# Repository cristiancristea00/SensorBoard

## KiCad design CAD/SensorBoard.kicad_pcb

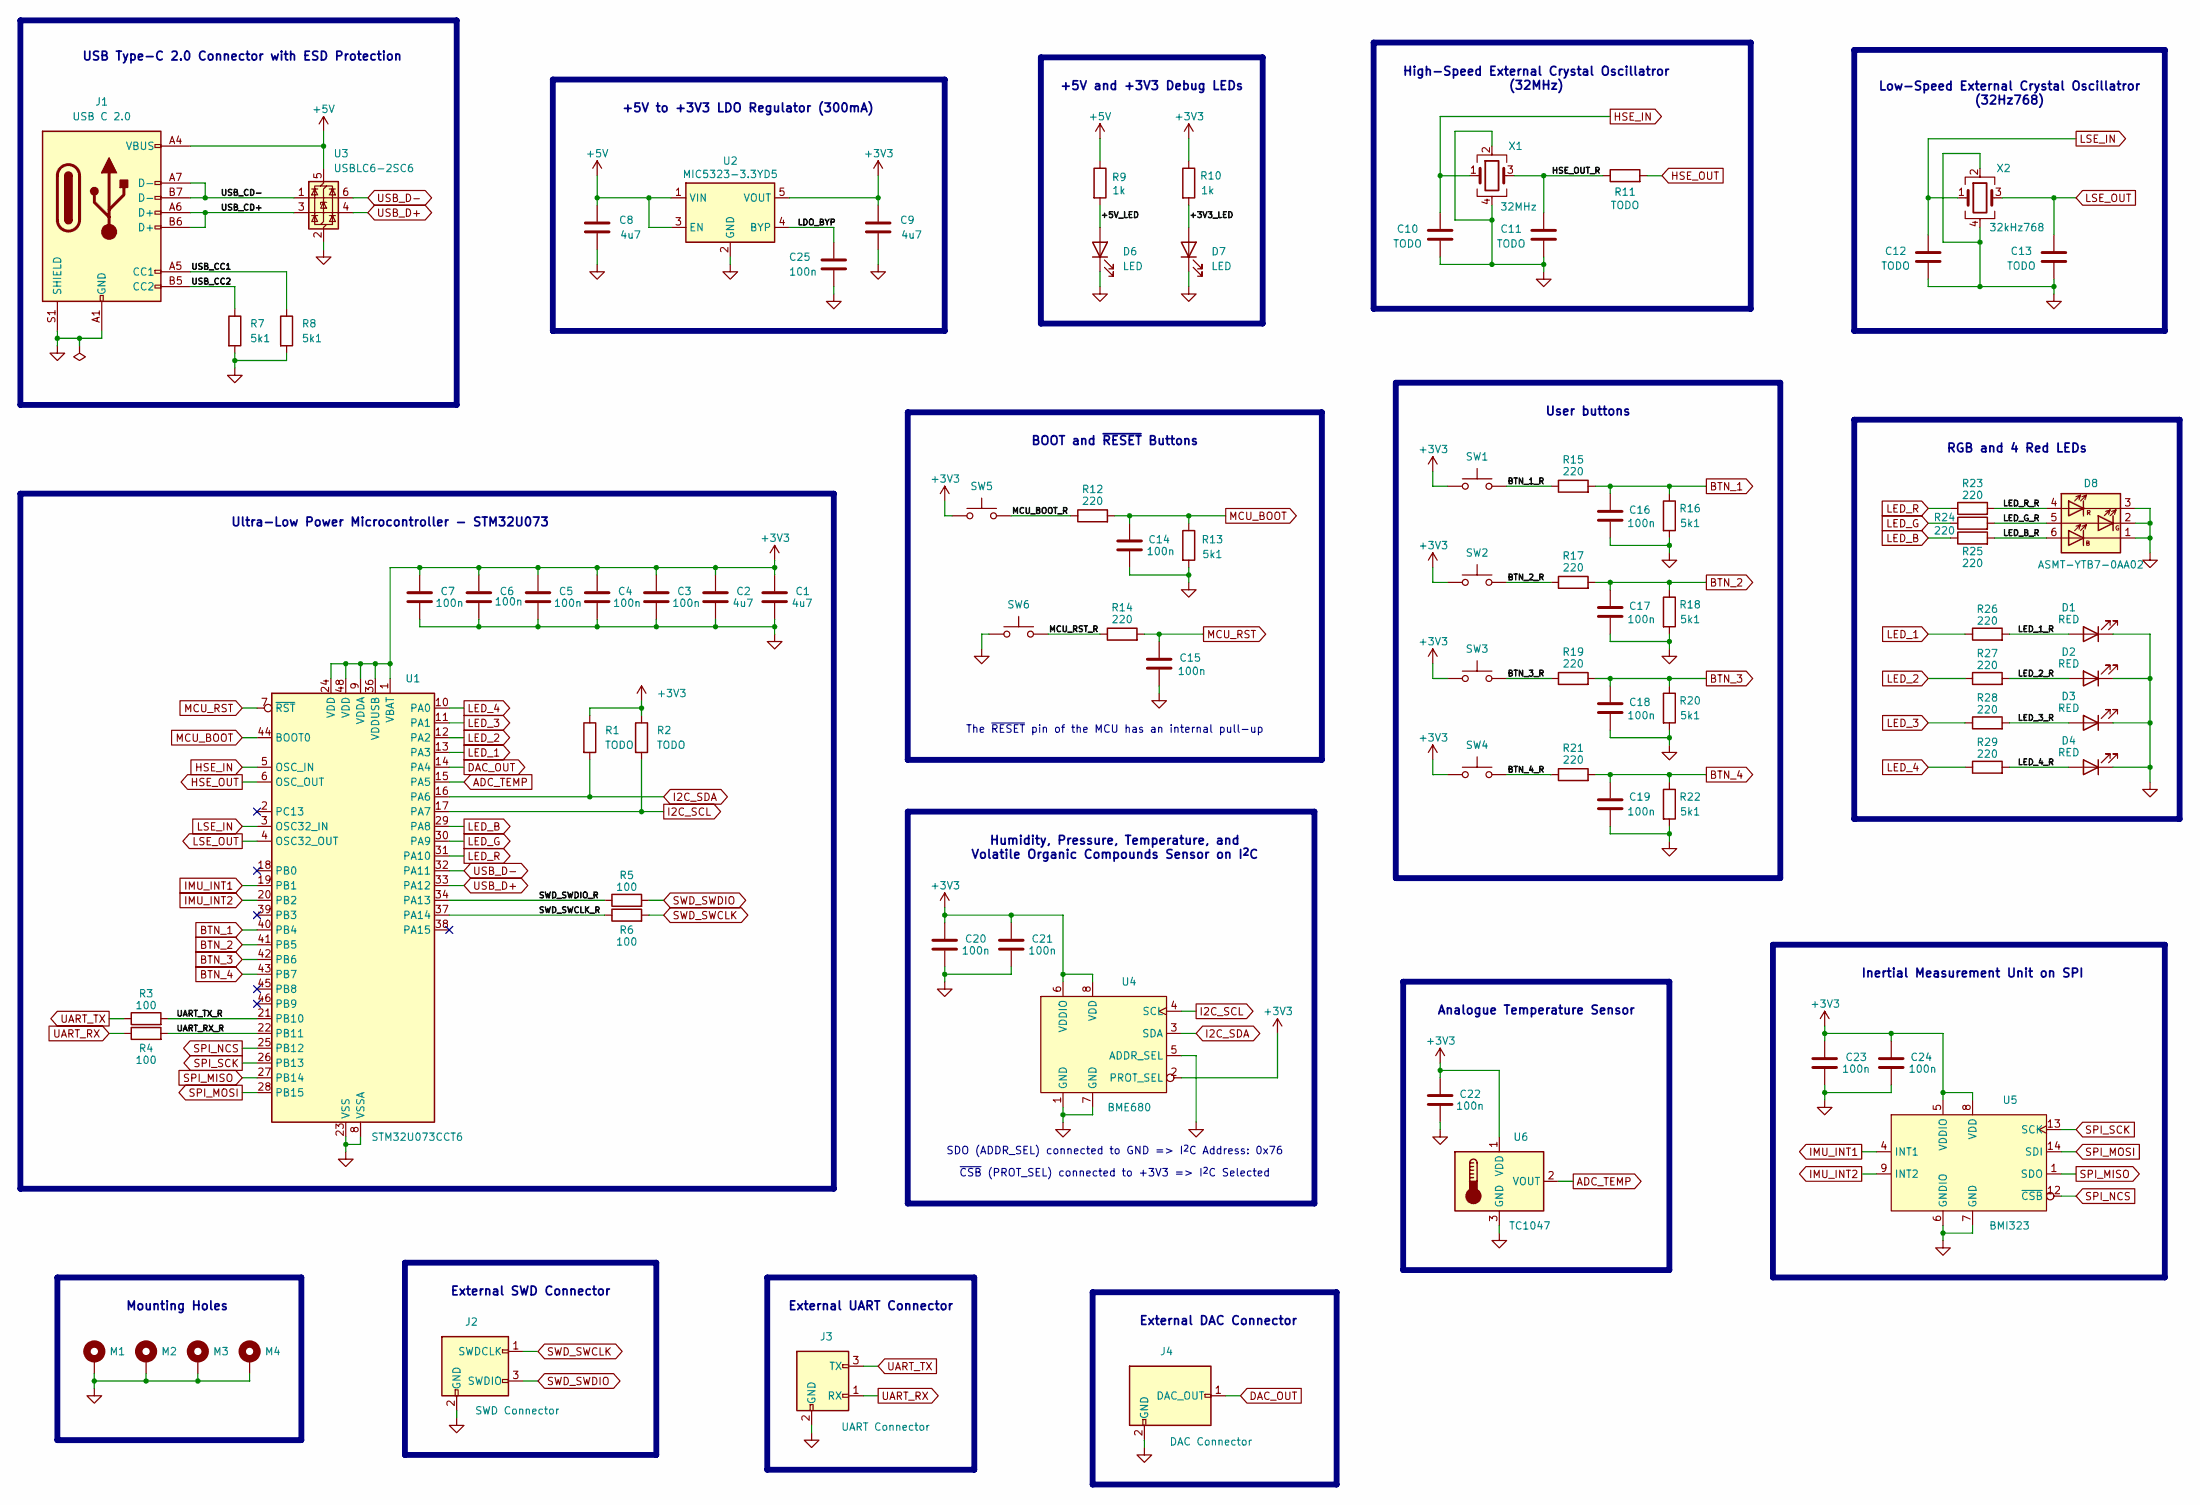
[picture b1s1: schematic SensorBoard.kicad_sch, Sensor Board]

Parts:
C1, C2, C8, C9: 4u7; C_0603_1608Metric
C3, C4, C5, C6, C7, C14, C15, C16, C17, C18, C19, C20, C21, C22, C23, C24: 100n; C_0402_1005Metric
C10, C11, C12, C13: TODO; C_0402_1005Metric
C25: 100n; C_0603_1608Metric
D1, D2, D3, D4: RED; LED_0805_2012Metric
D6, D7: LED; LED_0805_2012Metric
D8: ASMT-YTB7-0AA02
J1: USB C 2.0; USB_C_Receptacle_GCT_USB4105-xx-A_16P_TopMnt_Horizontal
J2: SWD Connector; SM03B-SR
J3: UART Connector; SM03B-SR
J4: DAC Connector; SM02B-SR
M1: M1; MountingHole_3.2mm_M3_Pad_Via
M2: M2; MountingHole_3.2mm_M3_Pad_Via
M3: M3; MountingHole_3.2mm_M3_Pad_Via
M4: M4; MountingHole_3.2mm_M3_Pad_Via
R1, R2, R11: TODO; R_0402_1005Metric
R3, R4, R5, R6: 100; R_0402_1005Metric
R7, R8, R13, R16, R18, R20, R22: 5k1; R_0402_1005Metric
R9, R10: 1k; R_0402_1005Metric
R12, R14, R15, R17, R19, R21, R23, R24, R25, R26, R27, R28, R29: 220; R_0402_1005Metric
SW1: SW_1; PTS636-SM25F-SMTR-LFS
SW2: SW_2; PTS636-SM25F-SMTR-LFS
SW3: SW_3; PTS636-SM25F-SMTR-LFS
SW4: SW_4; PTS636-SM25F-SMTR-LFS
SW5: SW_BOOT; PTS636-SM25F-SMTR-LFS
SW6: SW_RST; PTS636-SM25F-SMTR-LFS
U1: STM32U073CCT6; LQFP-48_7x7mm_P0.5mm
U2: MIC5323-3.3YD5; SOT-23-5
U3: USBLC6-2SC6; SOT-23-6
U4: BME680; BME630
U5: BMI323
U6: TC1047; SOT-23-3
X1: 32MHz; Crystal_SMD_2016-4Pin_2.0x1.6mm
X2: 32kHz768; Crystal_SMD_2016-4Pin_2.0x1.6mm

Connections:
+3V3: C1.2, C2.2, C3.2, C4.2, C5.2, C6.2, C7.2, C9.2, C20.2, C21.2, C22.2, C23.2, C24.2, R1.1, R2.1, R10.1, SW1.1, SW2.1, SW3.1, SW4.1, SW5.1, U1.1 (VBAT), U1.9 (VDDA), U1.24 (VDD), U1.36 (VDDUSB), U1.48 (VDD), U2.5 (VOUT), U4.2 (PROT_SEL), U4.6 (VDDIO), U4.8 (VDD), U5.5 (VDDIO), U5.8 (VDD), U6.1 (VDD)
+5V: C8.2, J1.A4 (VBUS), J1.A9 (VBUS), J1.B4 (VBUS), J1.B9 (VBUS), R9.1, U2.1 (VIN), U2.3 (EN), U3.5 (VBUS)
/+3V3_LED: D7.2 (A), R10.2
/+5V_LED: D6.2 (A), R9.2
/BTN_1_R: R15.1, SW1.2
/BTN_2_R: R17.1, SW2.2
/BTN_3_R: R19.1, SW3.2
/BTN_4_R: R21.1, SW4.2
/HSE_OUT_R: C11.1, R11.1, X1.3
/LDO_BYP: C25.2, U2.4 (BYP)
/LED_1_R: D1.2 (A), R26.2
/LED_2_R: D2.2 (A), R27.2
/LED_3_R: D3.2 (A), R28.2
/LED_4_R: D4.2 (A), R29.2
/LED_B_R: D8.6 (AB), R25.2
/LED_G_R: D8.5 (AG), R24.2
/LED_R_R: D8.4 (AR), R23.2
/MCU_BOOT_R: R12.1, SW5.2
/MCU_RST_R: R14.1, SW6.2
/SWD_SWCLK_R: R6.1, U1.37 (PA14)
/SWD_SWDIO_R: R5.1, U1.34 (PA13)
/UART_RX_R: R4.2, U1.22 (PB11)
/UART_TX_R: R3.2, U1.21 (PB10)
/USB_CC1: J1.A5 (CC1), R8.1
/USB_CC2: J1.B5 (CC2), R7.1
/USB_CD+: J1.A6 (D+), J1.B6 (D+), U3.3 (I/O2)
/USB_CD-: J1.A7 (D-), J1.B7 (D-), U3.1 (I/O1)
ADC_TEMP: U1.15 (PA5), U6.2 (VOUT)
BTN_1: C16.2, R15.2, R16.1, U1.40 (PB4)
BTN_2: C17.2, R17.2, R18.1, U1.41 (PB5)
BTN_3: C18.2, R19.2, R20.1, U1.42 (PB6)
BTN_4: C19.2, R21.2, R22.1, U1.43 (PB7)
DAC_OUT: J4.1 (DAC_OUT), U1.14 (PA4)
GND: C1.1, C2.1, C3.1, C4.1, C5.1, C6.1, C7.1, C8.1, C9.1, C10.2, C11.2, C12.2, C13.2, C14.1, C15.1, C16.1, C17.1, C18.1, C19.1, C20.1, C21.1, C22.1, C23.1, C24.1, C25.1, D1.1 (K), D2.1 (K), D3.1 (K), D4.1 (K), D6.1 (K), D7.1 (K), D8.1 (KB), D8.2 (KG), D8.3 (KR), J1.A1 (GND), J1.A12 (GND), J1.B1 (GND), J1.B12 (GND), J1.S1 (SHIELD), J2.2 (GND), J3.2 (GND), J4.2 (GND), M1.1, M2.1, M3.1, M4.1, R7.2, R8.2, R13.2, R16.2, R18.2, R20.2, R22.2, SW6.1, U1.8 (VSSA), U1.23 (VSS), U1.35 (VSS), U1.47 (VSS), U2.2 (GND), U3.2 (GND), U4.1 (GND), U4.5 (ADDR_SEL), U4.7 (GND), U5.6 (GNDIO), U5.7 (GND), U6.3 (GND), X1.2, X1.4, X2.2, X2.4
HSE_IN: C10.1, U1.5 (OSC_IN), X1.1
HSE_OUT: R11.2, U1.6 (OSC_OUT)
I2C_SCL: R2.2, U1.17 (PA7), U4.4 (SCL)
I2C_SDA: R1.2, U1.16 (PA6), U4.3 (SDA)
IMU_INT1: U1.19 (PB1), U5.4 (INT1)
IMU_INT2: U1.20 (PB2), U5.9 (INT2)
LED_1: R26.1, U1.13 (PA3)
LED_2: R27.1, U1.12 (PA2)
LED_3: R28.1, U1.11 (PA1)
LED_4: R29.1, U1.10 (PA0)
LED_B: R25.1, U1.29 (PA8)
LED_G: R24.1, U1.30 (PA9)
LED_R: R23.1, U1.31 (PA10)
LSE_IN: C12.1, U1.3 (OSC32_IN), X2.1
LSE_OUT: C13.1, U1.4 (OSC32_OUT), X2.3
MCU_BOOT: C14.2, R12.2, R13.1, U1.44 (BOOT0)
MCU_RST: C15.2, R14.2, U1.7 (~RST)
SPI_MISO: U1.27 (PB14), U5.1 (SDO)
SPI_MOSI: U1.28 (PB15), U5.14 (SDI)
SPI_NCS: U1.25 (PB12), U5.12 (~CSB)
SPI_SCK: U1.26 (PB13), U5.13 (SCK)
SWD_SWCLK: J2.1 (SWDCLK), R6.2
SWD_SWDIO: J2.3 (SWDIO), R5.2
UART_RX: J3.1 (RX), R4.1
UART_TX: J3.3 (TX), R3.1
USB_D+: U1.33 (PA12), U3.4 (I/O2)
USB_D-: U1.32 (PA11), U3.6 (I/O1)

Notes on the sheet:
The ~{RESET} pin of the MCU has an internal pull-up
User buttons
~{CSB} (PROT_SEL) connected to +3V3 => I^{2}C Selected
RGB and 4 Red LEDs
External UART Connector
External DAC Connector
Mounting Holes
+5V to +3V3 LDO Regulator (300mA)
BOOT and ~{RESET} Buttons
External SWD Connector
High-Speed External Crystal Oscillatror (32MHz)
Analogue Temperature Sensor
SDO (ADDR_SEL) connected to GND => I^{2}C Address: 0x76
USB Type-C 2.0 Connector with ESD Protection
Ultra-Low Power Microcontroller - STM32U073
Humidity, Pressure, Temperature, and Volatile Organic Compounds Sensor on I^{2}C
Low-Speed External Crystal Oscillatror (32Hz768)
+5V and +3V3 Debug LEDs
Inertial Measurement Unit on SPI

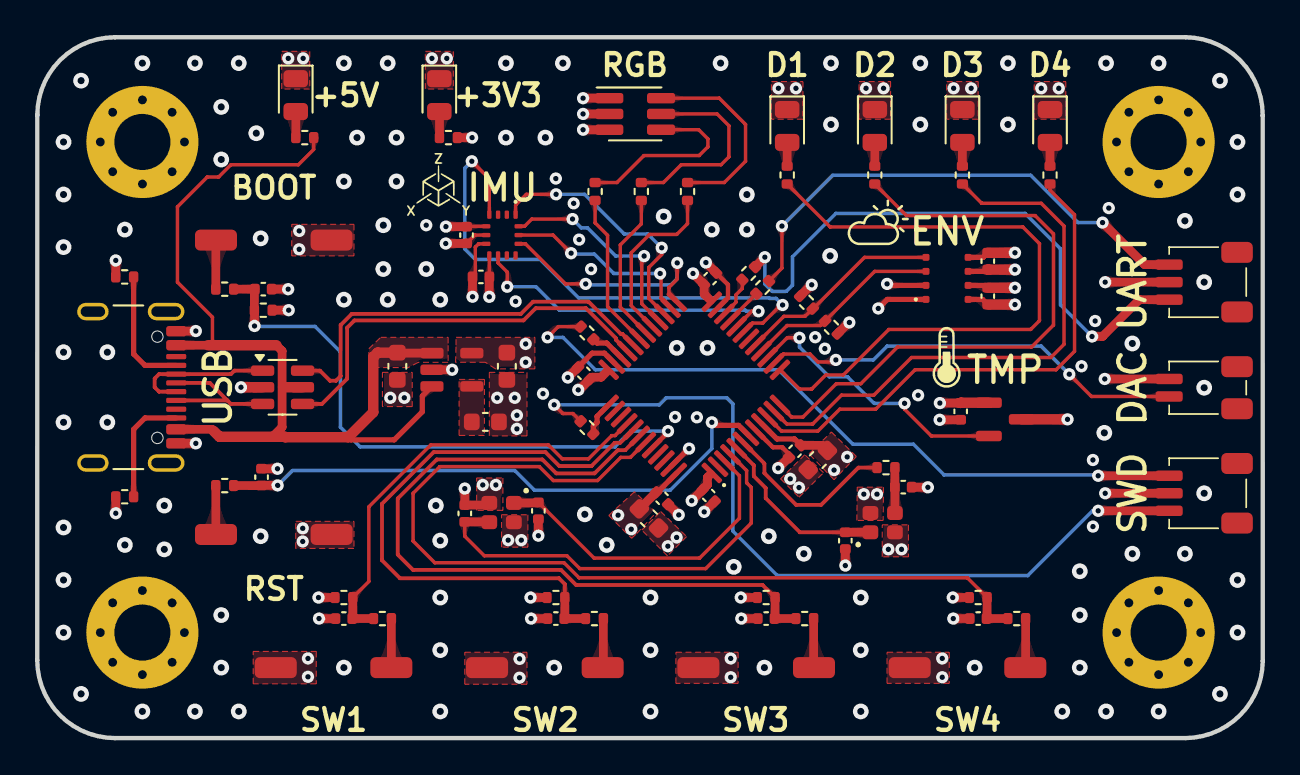
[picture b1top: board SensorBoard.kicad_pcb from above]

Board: 4 copper layers, 69.9 x 40.0 mm, 83 parts (0 on the bottom side), 61 nets.

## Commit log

2024-06-22 Add initial project structure
2024-06-22 Add MCU symbol
2024-06-22 Add crystal oscillators to schematic
2024-06-22 Add BOOT button
2024-06-23 Further progress with power and peripherals
2024-06-23 Add BMI323 symbol and footprint
2024-06-23 Update BME630 footprint
2024-06-23 Add net classes
2024-06-23 Add I2C and SPI connections
2024-06-24 Add LEDs and buttons
2024-06-24 Add external connectors
2024-06-25 Schematic clean-up
2024-06-25 Add basic PCB settings
2024-06-25 Update connector footprints and RGB LED
2024-06-25 Update net classes
2024-06-25 Begin initial PCB design
2024-06-25 Add updates to footprints
2024-06-26 Update and add more footprints
2024-06-26 Update oscillator footprint
2024-06-28 Finish rough components placement
2024-06-30 Add initial traces and vias
2024-06-30 Add initial silkscreen clean-up
2024-07-02 Add keepout for sensors and clean silkscreen
2024-07-03 Implement some feedback from Grig
2024-07-11 Update some placement of componenets and silkscreen
2024-07-11 Add stitching vias and silkscreen icons
2024-07-12 Update LDO
2024-07-12 Update silkscreen
2024-07-12 Add keepout for crystals
2024-07-12 Update silkscreen font
